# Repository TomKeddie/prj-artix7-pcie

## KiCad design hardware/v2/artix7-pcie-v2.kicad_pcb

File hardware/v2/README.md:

# PCIe artix7

## serdes
- x1 pcie connector (check serdes allocation)
- x1 usb3 connector for expanders and RPi
- x1 on SMA connectors
- x1 in loop?

## Power supply
- reuse supply from netv2

## PMODs
- lots

## CMOD
- maybe

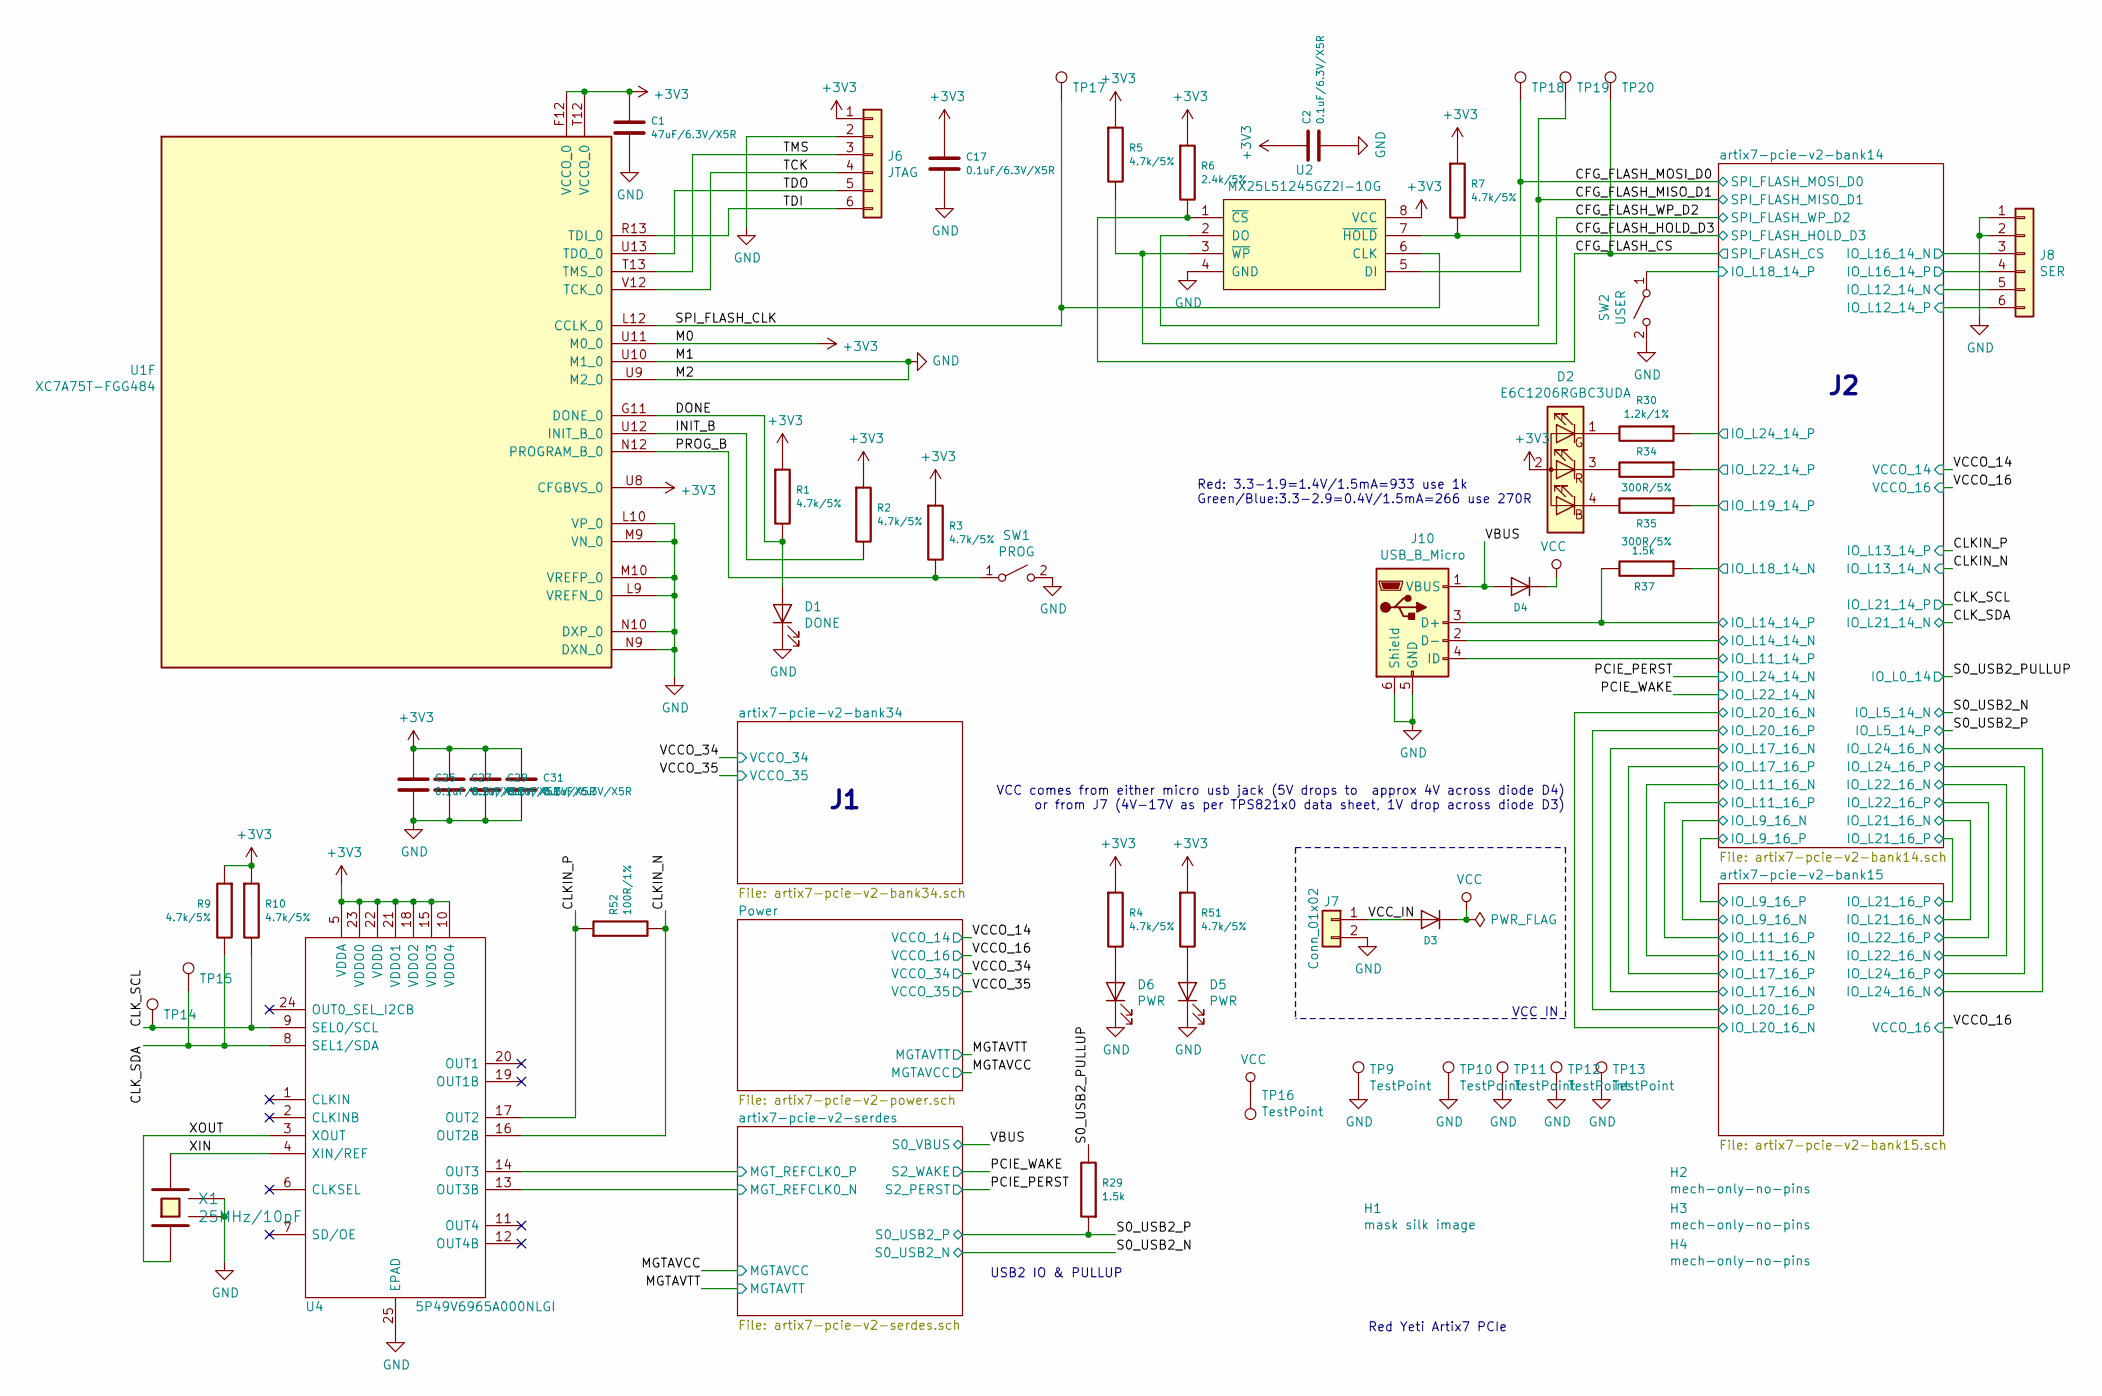
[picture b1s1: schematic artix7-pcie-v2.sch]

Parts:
C1: 47uF/6.3V/X5R; C_1206_3216Metric; LCSC C96123
C2, C17, C25, C27, C29, C31: 0.1uF/6.3V/X5R; C_0402_1005Metric; LCSC C1525
D1: DONE; LED_0402_1005Metric; LCSC C130722
D2: E6C1206RGBC3UDA; LCSC C375571
D3, D4: SBR3U20SA-13; D_SMA; LCSC C146738
D5, D6: PWR; LED_0402_1005Metric; LCSC C130724
H1: mask silk image; mask; LCSC DNP
H2, H3, H4: mech-only-no-pins; JLCPCB_ASSEMBLY_TOOL_HOLE; LCSC DNP
J6: JTAG; PinHeader_2x03_P2.54mm_Vertical; LCSC DNP
J7: Conn_01x02; JST-2-SMD; LCSC DNP
J8: SER; PinHeader_2x03_P2.54mm_Vertical; LCSC DNP
J10: USB_B_Micro; USB_MICRO_TAOBAO_SMD_PTH; LCSC DNP
R1, R2, R3, R4, R5, R7, R9, R10, R51: 4.7k/5%; R_0402_1005Metric; LCSC C25900
R6: 2.4k/5%; R_0402_1005Metric; LCSC C25882
R29, R37: 1.5k; R_0402_1005Metric; LCSC C25867
R30: 1.2k/1%; R_0402_1005Metric; LCSC C25862
R34, R35: 300R/5%; R_0402_1005Metric; LCSC C25102
R52: 100R/1%; R_0402_1005Metric; LCSC C25076
SW1: PROG; SW_Push_1P1T_NO_Vertical_Wuerth_434133025816; LCSC DNP
SW2: USER; SW_Push_1P1T_NO_Vertical_Wuerth_434133025816; LCSC DNP
TP9: TestPoint; TestPoint_Loop_D2.50mm_Drill1.0mm; LCSC DNP
TP10, TP11, TP12, TP13: TestPoint; MountingHole_2.7mm_M2.5_DIN965_Pad; LCSC DNP
TP14: SCL; TestPoint_Pad_D1.5mm; LCSC DNP
TP15: SDA; TestPoint_Pad_D1.5mm; LCSC DNP
TP16, TP17, TP18, TP19, TP20: TestPoint; TestPoint_Pad_D1.5mm; LCSC DNP
U1: XC7A75T-FGG484; Xilinx_FGG484; LCSC DNP
U2: MX25L51245GZ2I-10G; WSON-8-1EP_8x6mm_P1.27mm; LCSC DNP
U4: 5P49V6965A000NLGI; QFN50P400X400X100-25N-D; Mouser Part Number 972-49V6965A000NLGI
X1: 25MHz/10pF; Crystal_SMD_3225-4Pin_3.2x2.5mm; LCSC C9006

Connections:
+3V3: C1.1, C2.1, C17.1, C25.1, C27.1, C29.1, C31.1, D2.2 (A), J6.1, R1.1, R2.1, R3.1, R4.1, R5.1, R6.1, R7.1, R9.1, R10.1, R51.1, U1.F12 (VCCO_0), U1.T12 (VCCO_0), U1.U8 (CFGBVS_0), U1.U11 (M0_0), U2.8 (VCC), U4.5 (VDDA), U4.10 (VDDO4), U4.15 (VDDO3), U4.18 (VDDO2), U4.21 (VDDO1), U4.22 (VDDD), U4.23 (VDDO0); also elsewhere on the board
/CFG_FLASH_CS: R6.2, TP20.1, U2.1 (~CS); also elsewhere on the board
/CFG_FLASH_HOLD_D3: R7.2, U2.7 (~HOLD); also elsewhere on the board
/CFG_FLASH_MISO_D1: TP19.1, U2.2 (DO); also elsewhere on the board
/CFG_FLASH_MOSI_D0: TP18.1, U2.5 (DI); also elsewhere on the board
/CFG_FLASH_WP_D2: R5.2, U2.3 (~WP); also elsewhere on the board
/CLKIN_N: R52.2, U4.16 (OUT2B); also elsewhere on the board
/CLKIN_P: R52.1, U4.17 (OUT2); also elsewhere on the board
/CLK_SCL: R10.2, TP14.1, U4.9 (SEL0/SCL); also elsewhere on the board
/CLK_SDA: R9.2, TP15.1, U4.8 (SEL1/SDA); also elsewhere on the board
/DONE: D1.2 (A), R1.2, U1.G11 (DONE_0)
/INIT_B: R2.2, U1.U12 (INIT_B_0)
/PROG_B: R3.2, SW1.1 (A), U1.N12 (PROGRAM_B_0)
/S0_USB2_P: R29.1; also elsewhere on the board
/S0_USB2_PULLUP: R29.2; also elsewhere on the board
/SPI_FLASH_CLK: TP17.1, U1.L12 (CCLK_0), U2.6 (CLK)
/TCK: J6.4, U1.V12 (TCK_0)
/TDI: J6.6, U1.R13 (TDI_0)
/TDO: J6.5, U1.U13 (TDO_0)
/TMS: J6.3, U1.T13 (TMS_0)
/VBUS: D4.2 (A), J10.1 (VBUS); also elsewhere on the board
/VCC_IN: D3.2 (A), J7.1
/XIN: U4.4 (XIN/REF), X1.3
/XOUT: U4.3 (XOUT), X1.1
/artix7-pcie-v2-bank14/IO_L11_14_P: J10.4 (ID); also elsewhere on the board
/artix7-pcie-v2-bank14/IO_L12_14_N: J8.5; also elsewhere on the board
/artix7-pcie-v2-bank14/IO_L12_14_P: J8.6; also elsewhere on the board
/artix7-pcie-v2-bank14/IO_L14_14_N: J10.2 (D-); also elsewhere on the board
/artix7-pcie-v2-bank14/IO_L14_14_P: J10.3 (D+), R37.2; also elsewhere on the board
/artix7-pcie-v2-bank14/IO_L16_14_N: J8.3; also elsewhere on the board
/artix7-pcie-v2-bank14/IO_L16_14_P: J8.4; also elsewhere on the board
/artix7-pcie-v2-bank14/IO_L18_14_N: R37.1; also elsewhere on the board
/artix7-pcie-v2-bank14/IO_L18_14_P: SW2.1 (A); also elsewhere on the board
/artix7-pcie-v2-bank14/IO_L19_14_P: R35.1; also elsewhere on the board
/artix7-pcie-v2-bank14/IO_L22_14_P: R34.1; also elsewhere on the board
/artix7-pcie-v2-bank14/IO_L24_14_P: R30.1; also elsewhere on the board
/artix7-pcie-v2-serdes/MGT_REFCLK0_N: U4.13 (OUT3B); also elsewhere on the board
/artix7-pcie-v2-serdes/MGT_REFCLK0_P: U4.14 (OUT3); also elsewhere on the board
GND: C1.2, C2.2, C17.2, C25.2, C27.2, C29.2, C31.2, D1.1 (K), D5.1 (K), D6.1 (K), J6.2, J7.2, J8.1, J8.2, J10.5 (GND), J10.6 (Shield), SW1.2 (B), SW2.2 (B), TP9.1, TP10.1, TP11.1, TP12.1, TP13.1, U1.L9 (VREFN_0), U1.L10 (VP_0), U1.M9 (VN_0), U1.M10 (VREFP_0), U1.N9 (DXN_0), U1.N10 (DXP_0), U1.U9 (M2_0), U1.U10 (M1_0), U2.4 (GND), U4.25 (EPAD), X1.2 (GND), X1.4 (GND); also elsewhere on the board
unnamed: D2.1 (G), R30.2
unnamed: D2.3 (R), R34.2
unnamed: D2.4 (B), R35.2
unnamed: D5.2 (A), R51.2
unnamed: D6.2 (A), R4.2
VCC: D3.1 (K), D4.1 (K), TP16.1; also elsewhere on the board

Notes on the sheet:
USB2 IO & PULLUP
VCC IN
Red: 3.3-1.9=1.4V/1.5mA=933 use 1k Green/Blue:3.3-2.9=0.4V/1.5mA=266 use 270R
VCC comes from either micro usb jack (5V drops to approx 4V across diode D4) or from J7 (4V-17V as per TPS821x0 data sheet, 1V drop across diode D3)
Red Yeti Artix7 PCIe

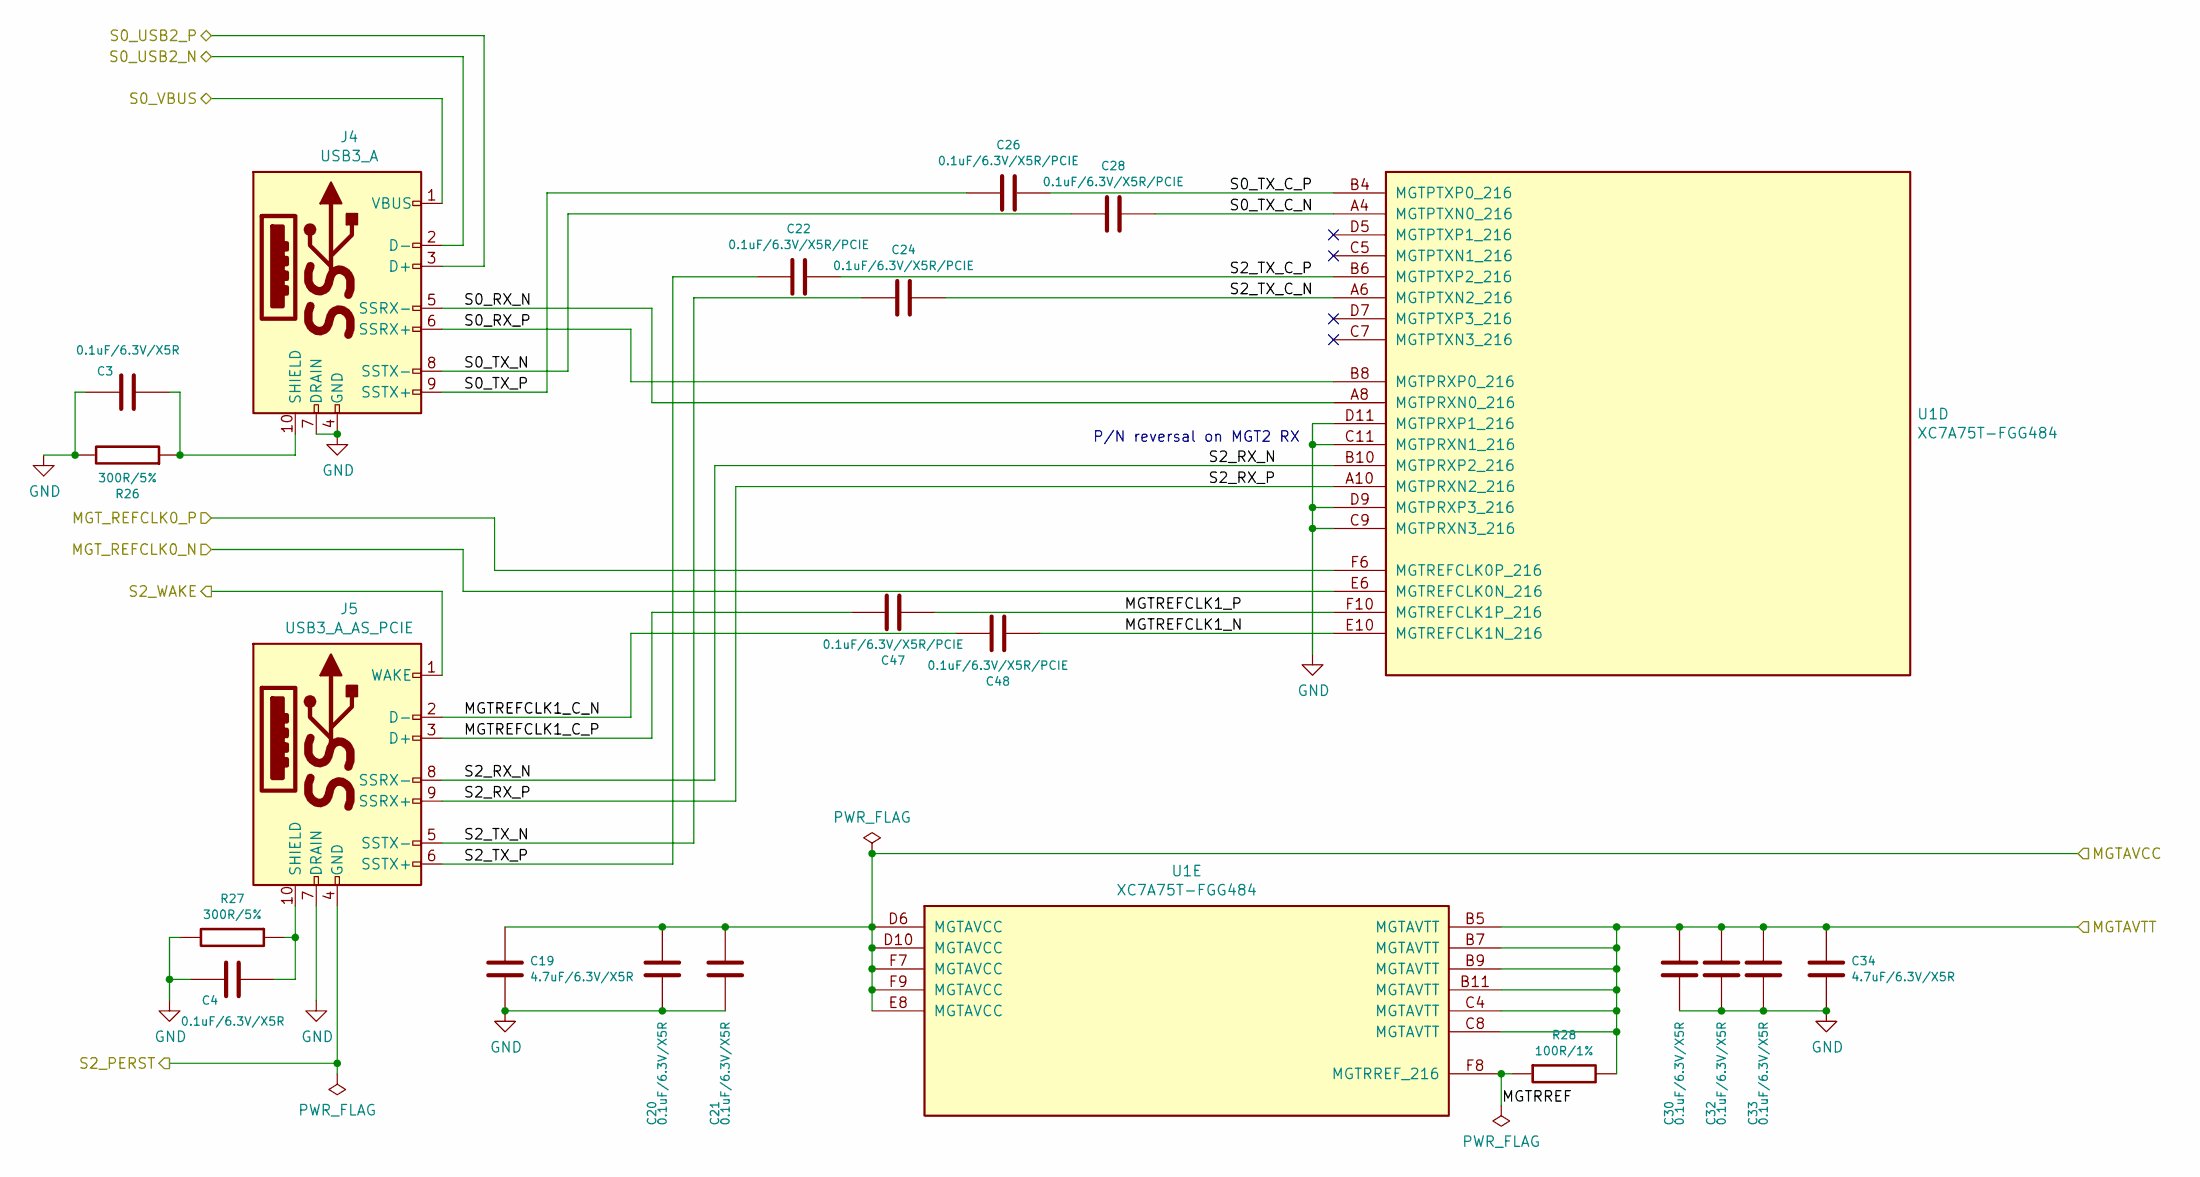
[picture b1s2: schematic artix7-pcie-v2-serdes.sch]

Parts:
C3, C4, C20, C21, C30, C32, C33: 0.1uF/6.3V/X5R; C_0402_1005Metric; LCSC C1525
C19, C34: 4.7uF/6.3V/X5R; C_0402_1005Metric; LCSC C23733
C22, C24, C26, C28, C47, C48: 0.1uF/6.3V/X5R/PCIE; C_0402_1005Metric; LCSC C1525
J4: USB3_A; USB3_A_Aliexpress; Digikey 2057-USB-A3-S-RA-ND
J5: USB3_A_AS_PCIE; USB3_A_Aliexpress; Digikey 2057-USB-A3-S-RA-ND
R26, R27: 300R/5%; R_0402_1005Metric; LCSC C25102
R28: 100R/1%; R_0402_1005Metric; LCSC C25076
U1: XC7A75T-FGG484; Xilinx_FGG484; LCSC DNP

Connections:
+1V0: C19.1, C20.1, C21.1, U1.D6 (MGTAVCC), U1.D10 (MGTAVCC), U1.E8 (MGTAVCC), U1.F7 (MGTAVCC), U1.F9 (MGTAVCC); also elsewhere on the board
/MGTAVTT: C30.1, C32.1, C33.1, C34.1, R28.2, U1.B5 (MGTAVTT), U1.B7 (MGTAVTT), U1.B9 (MGTAVTT), U1.B11 (MGTAVTT), U1.C4 (MGTAVTT), U1.C8 (MGTAVTT); also elsewhere on the board
/PCIE_PERST: J5.4 (GND); also elsewhere on the board
/PCIE_WAKE: J5.1 (WAKE); also elsewhere on the board
/S0_USB2_N: J4.2 (D-); also elsewhere on the board
/S0_USB2_P: J4.3 (D+); also elsewhere on the board
/VBUS: J4.1 (VBUS); also elsewhere on the board
/artix7-pcie-v2-serdes/MGTREFCLK1_C_N: C48.2, J5.2 (D-)
/artix7-pcie-v2-serdes/MGTREFCLK1_C_P: C47.2, J5.3 (D+)
/artix7-pcie-v2-serdes/MGTREFCLK1_N: C48.1, U1.E10 (MGTREFCLK1N_216)
/artix7-pcie-v2-serdes/MGTREFCLK1_P: C47.1, U1.F10 (MGTREFCLK1P_216)
/artix7-pcie-v2-serdes/MGTRREF: R28.1, U1.F8 (MGTRREF_216)
/artix7-pcie-v2-serdes/MGT_REFCLK0_N: U1.E6 (MGTREFCLK0N_216); also elsewhere on the board
/artix7-pcie-v2-serdes/MGT_REFCLK0_P: U1.F6 (MGTREFCLK0P_216); also elsewhere on the board
/artix7-pcie-v2-serdes/S0_RX_N: J4.5 (SSRX-), U1.A8 (MGTPRXN0_216)
/artix7-pcie-v2-serdes/S0_RX_P: J4.6 (SSRX+), U1.B8 (MGTPRXP0_216)
/artix7-pcie-v2-serdes/S0_TX_C_N: C28.1, U1.A4 (MGTPTXN0_216)
/artix7-pcie-v2-serdes/S0_TX_C_P: C26.1, U1.B4 (MGTPTXP0_216)
/artix7-pcie-v2-serdes/S0_TX_N: C28.2, J4.8 (SSTX-)
/artix7-pcie-v2-serdes/S0_TX_P: C26.2, J4.9 (SSTX+)
/artix7-pcie-v2-serdes/S2_RX_N: J5.8 (SSRX-), U1.B10 (MGTPRXP2_216)
/artix7-pcie-v2-serdes/S2_RX_P: J5.9 (SSRX+), U1.A10 (MGTPRXN2_216)
/artix7-pcie-v2-serdes/S2_TX_C_N: C24.1, U1.A6 (MGTPTXN2_216)
/artix7-pcie-v2-serdes/S2_TX_C_P: C22.1, U1.B6 (MGTPTXP2_216)
/artix7-pcie-v2-serdes/S2_TX_N: C24.2, J5.5 (SSTX-)
/artix7-pcie-v2-serdes/S2_TX_P: C22.2, J5.6 (SSTX+)
GND: C3.2, C4.2, C19.2, C20.2, C21.2, C30.2, C32.2, C33.2, C34.2, J4.4 (GND), J4.7 (DRAIN), J5.7 (DRAIN), R26.2, R27.2, U1.C9 (MGTPRXN3_216), U1.C11 (MGTPRXN1_216), U1.D9 (MGTPRXP3_216), U1.D11 (MGTPRXP1_216); also elsewhere on the board
unnamed: C3.1, J4.10 (SHIELD), R26.1
unnamed: C4.1, J5.10 (SHIELD), R27.1

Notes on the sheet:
P/N reversal on MGT2 RX

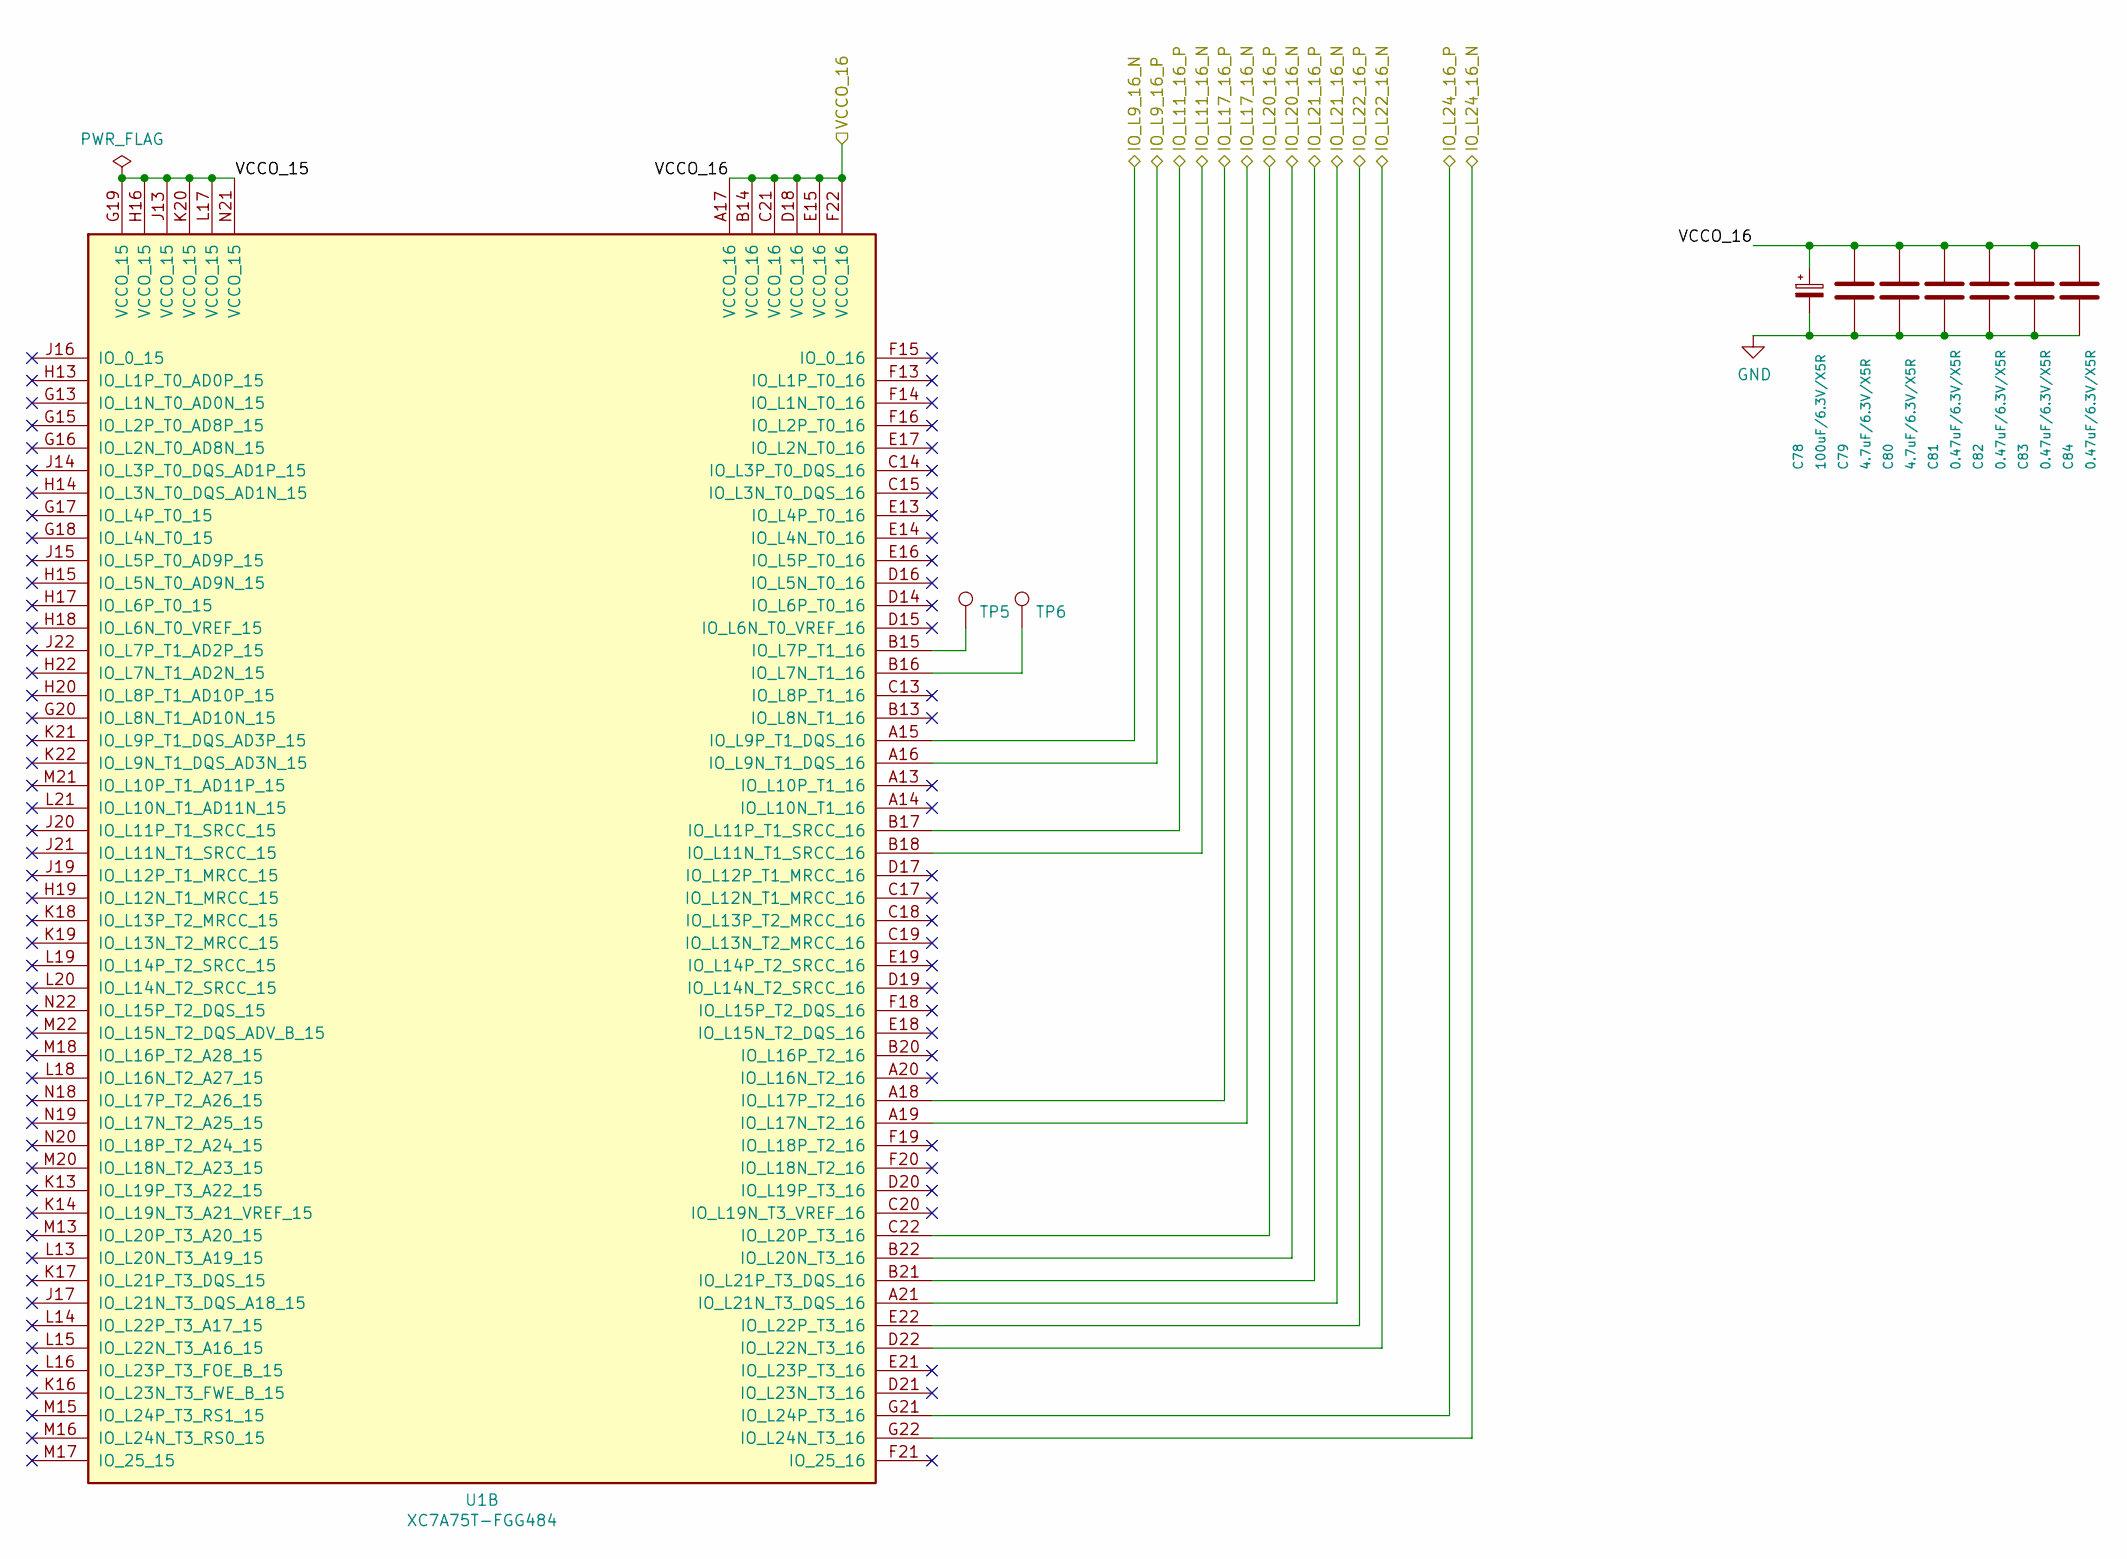
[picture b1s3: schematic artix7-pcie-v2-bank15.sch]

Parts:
C78: 100uF/6.3V/X5R; CP_EIA-3528-15_AVX-H; LCSC C16133
C79, C80: 4.7uF/6.3V/X5R; C_0402_1005Metric; LCSC C23733
C81, C82, C83, C84: 0.47uF/6.3V/X5R; C_0402_1005Metric; LCSC C47339
TP5, TP6: TestPoint; TestPoint_Pad_D1.5mm; LCSC DNP
U1: XC7A75T-FGG484; Xilinx_FGG484; LCSC DNP

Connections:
/VCCO_16: C78.1, C79.1, C80.1, C81.1, C82.1, C83.1, C84.1, U1.A17 (VCCO_16), U1.B14 (VCCO_16), U1.C21 (VCCO_16), U1.D18 (VCCO_16), U1.E15 (VCCO_16), U1.F22 (VCCO_16); also elsewhere on the board
/artix7-pcie-v2-bank14/IO_L9_16_N: U1.A15 (IO_L9P_T1_DQS_16); also elsewhere on the board
/artix7-pcie-v2-bank14/IO_L9_16_P: U1.A16 (IO_L9N_T1_DQS_16); also elsewhere on the board
/artix7-pcie-v2-bank14/IO_L11_16_N: U1.B18 (IO_L11N_T1_SRCC_16); also elsewhere on the board
/artix7-pcie-v2-bank14/IO_L11_16_P: U1.B17 (IO_L11P_T1_SRCC_16); also elsewhere on the board
/artix7-pcie-v2-bank14/IO_L17_16_N: U1.A19 (IO_L17N_T2_16); also elsewhere on the board
/artix7-pcie-v2-bank14/IO_L17_16_P: U1.A18 (IO_L17P_T2_16); also elsewhere on the board
/artix7-pcie-v2-bank14/IO_L20_16_N: U1.B22 (IO_L20N_T3_16); also elsewhere on the board
/artix7-pcie-v2-bank14/IO_L20_16_P: U1.C22 (IO_L20P_T3_16); also elsewhere on the board
/artix7-pcie-v2-bank14/IO_L21_16_N: U1.A21 (IO_L21N_T3_DQS_16); also elsewhere on the board
/artix7-pcie-v2-bank14/IO_L21_16_P: U1.B21 (IO_L21P_T3_DQS_16); also elsewhere on the board
/artix7-pcie-v2-bank14/IO_L22_16_N: U1.D22 (IO_L22N_T3_16); also elsewhere on the board
/artix7-pcie-v2-bank14/IO_L22_16_P: U1.E22 (IO_L22P_T3_16); also elsewhere on the board
/artix7-pcie-v2-bank14/IO_L24_16_N: U1.G22 (IO_L24N_T3_16); also elsewhere on the board
/artix7-pcie-v2-bank14/IO_L24_16_P: U1.G21 (IO_L24P_T3_16); also elsewhere on the board
/artix7-pcie-v2-bank15/VCCO_15: U1.G19 (VCCO_15), U1.H16 (VCCO_15), U1.J13 (VCCO_15), U1.K20 (VCCO_15), U1.L17 (VCCO_15), U1.N21 (VCCO_15)
GND: C78.2, C79.2, C80.2, C81.2, C82.2, C83.2, C84.2; also elsewhere on the board
unnamed: TP5.1, U1.B15 (IO_L7P_T1_16)
unnamed: TP6.1, U1.B16 (IO_L7N_T1_16)

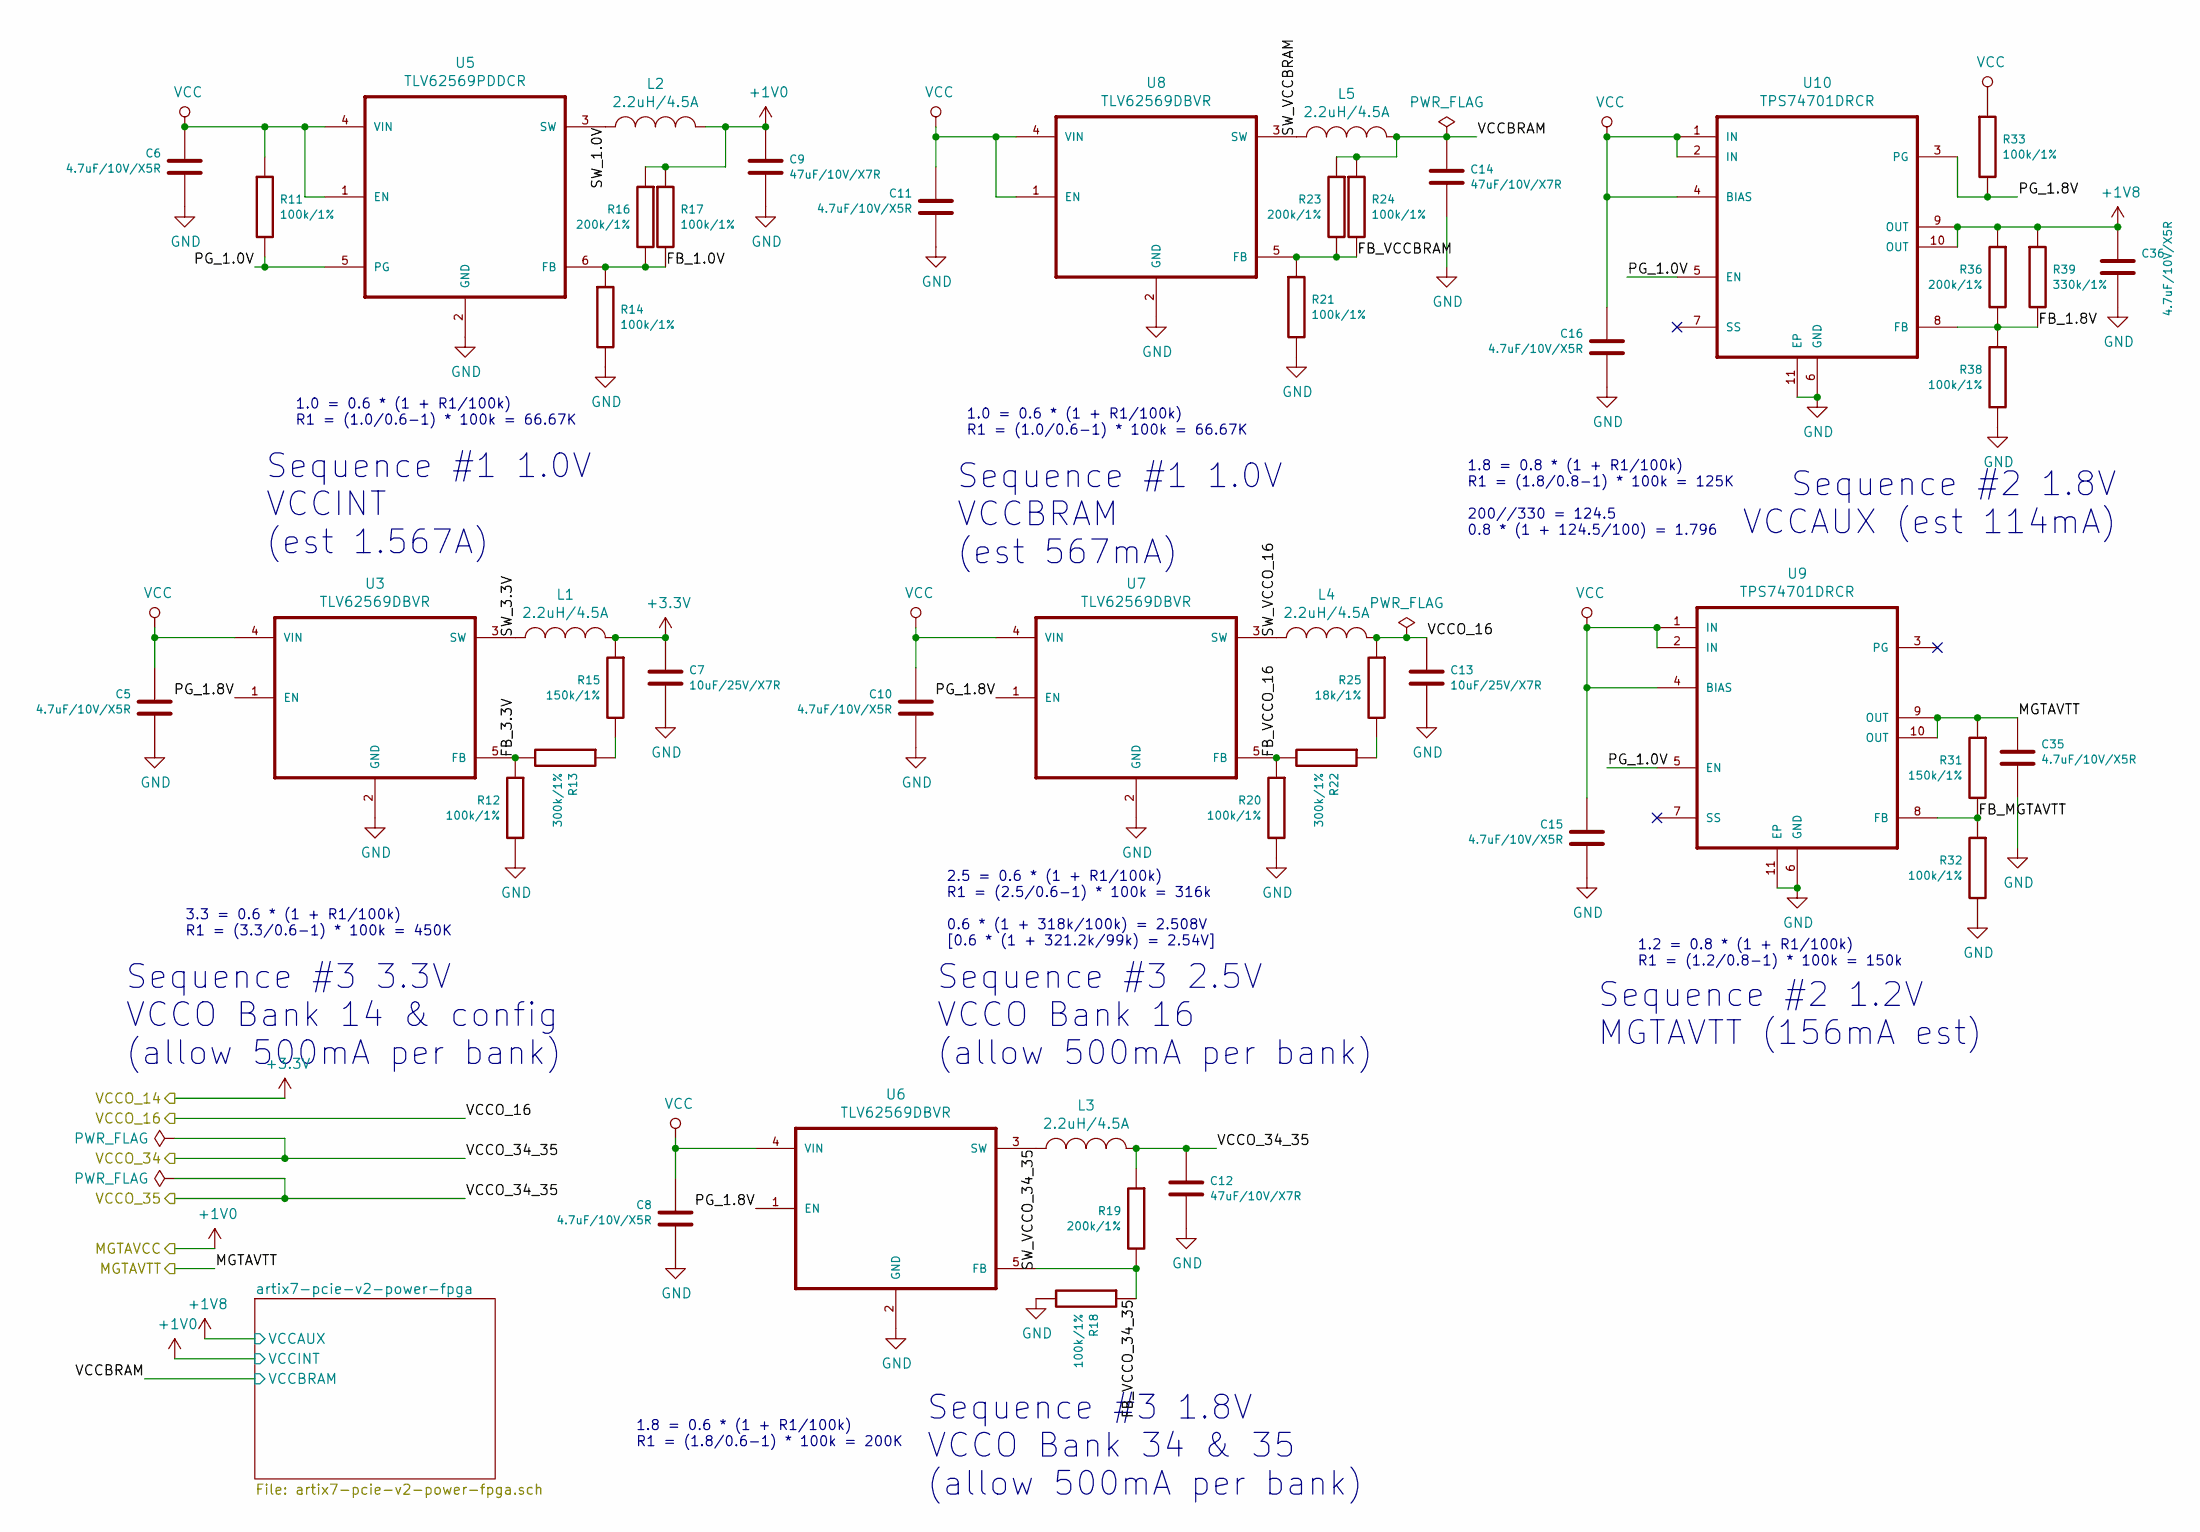
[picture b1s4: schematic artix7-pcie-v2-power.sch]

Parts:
C5, C6, C8, C10, C11, C15, C16, C35, C36: 4.7uF/10V/X5R; C_0402_1005Metric; LCSC C23733
C7, C13: 10uF/25V/X7R; C_1206_3216Metric; MFGPN C3216X7R1E106M160AE; LCSC C13585
C9, C12, C14: 47uF/10V/X7R; C_1206_3216Metric; LCSC C96123
L1, L2, L3, L4, L5: 2.2uH/4.5A; L_MWSA0518S; MPN MWSA0518S-2R2MT; LCSC C408345
R11, R12, R14, R17, R18, R20, R21, R24, R32, R33, R38: 100k/1%; R_0402_1005Metric; LCSC C25741
R13, R22: 300k/1%; R_0402_1005Metric; LCSC C25774
R15, R31: 150k/1%; R_0402_1005Metric; LCSC C25755
R16, R19, R23, R36: 200k/1%; R_0402_1005Metric; LCSC C25764
R25: 18k/1%; R_0402_1005Metric; LCSC C25762
R39: 330k/1%; R_0402_1005Metric; LCSC C25778
U3, U6, U7, U8: TLV62569DBVR; SOT95P280X145-5N; LCSC C141836
U5: TLV62569PDDCR; SOT95P280X110-6N; LCSC DNP
U9, U10: TPS74701DRCR; 16624-01YE; LCSC C105262

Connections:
+1V0: C9.2, L2.2, R16.1, R17.1; also elsewhere on the board
+1V8: C36.2, R36.1, R39.1, U10.9 (OUT), U10.10 (OUT); also elsewhere on the board
+3V3: C7.2, L1.2, R15.1; also elsewhere on the board
/MGTAVTT: C35.2, R31.1, U9.9 (OUT), U9.10 (OUT); also elsewhere on the board
/Power/FB_1.0V: R14.1, R16.2, R17.2, U5.6 (FB)
/Power/FB_1.8V: R36.2, R38.1, R39.2, U10.8 (FB)
/Power/FB_3.3V: R12.1, R13.2, U3.5 (FB)
/Power/FB_MGTAVTT: R31.2, R32.1, U9.8 (FB)
/Power/FB_VCCBRAM: R21.1, R23.2, R24.2, U8.5 (FB)
/Power/FB_VCCO_16: R20.1, R22.2, U7.5 (FB)
/Power/FB_VCCO_34_35: R18.1, R19.2, U6.5 (FB)
/Power/PG_1.0V: R11.2, U5.5 (PG), U9.5 (EN), U10.5 (EN)
/Power/PG_1.8V: R33.2, U3.1 (EN), U6.1 (EN), U7.1 (EN), U10.3 (PG)
/Power/SW_1.0V: L2.1, U5.3 (SW)
/Power/SW_3.3V: L1.1, U3.3 (SW)
/Power/SW_VCCBRAM: L5.1, U8.3 (SW)
/Power/SW_VCCO_16: L4.1, U7.3 (SW)
/Power/SW_VCCO_34_35: L3.1, U6.3 (SW)
/Power/VCCBRAM: C14.2, L5.2, R23.1, R24.1; also elsewhere on the board
/VCCO_16: C13.2, L4.2, R25.1; also elsewhere on the board
/VCCO_34: C12.2, L3.2, R19.1; also elsewhere on the board
GND: C5.1, C6.1, C7.1, C8.1, C9.1, C10.1, C11.1, C12.1, C13.1, C14.1, C15.1, C16.1, C35.1, C36.1, R12.2, R14.2, R18.2, R20.2, R21.2, R32.2, R38.2, U3.2 (GND), U5.2 (GND), U6.2 (GND), U7.2 (GND), U8.2 (GND), U9.6 (GND), U9.11 (EP), U10.6 (GND), U10.11 (EP); also elsewhere on the board
unnamed: R13.1, R15.2
unnamed: R22.1, R25.2
VCC: C5.2, C6.2, C8.2, C10.2, C11.2, C15.2, C16.2, R11.1, R33.1, U3.4 (VIN), U5.1 (EN), U5.4 (VIN), U6.4 (VIN), U7.4 (VIN), U8.1 (EN), U8.4 (VIN), U9.1 (IN), U9.2 (IN), U9.4 (BIAS), U10.1 (IN), U10.2 (IN), U10.4 (BIAS); also elsewhere on the board

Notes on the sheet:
1.0 = 0.6 * (1 + R1/100k) R1 = (1.0/0.6-1) * 100k = 66.67K
Sequence #1 1.0V VCCINT (est 1.567A)
Sequence #1 1.0V VCCBRAM (est 567mA)
Sequence #2 1.8V VCCAUX (est 114mA)
1.8 = 0.8 * (1 + R1/100k) R1 = (1.8/0.8-1) * 100k = 125K 200//330 = 124.5 0.8 * (1 + 124.5/100) = 1.796
1.2 = 0.8 * (1 + R1/100k) R1 = (1.2/0.8-1) * 100k = 150k
Sequence #2 1.2V MGTAVTT (156mA est)
Sequence #3 3.3V VCCO Bank 14 & config (allow 500mA per bank)
3.3 = 0.6 * (1 + R1/100k) R1 = (3.3/0.6-1) * 100k = 450K
2.5 = 0.6 * (1 + R1/100k) R1 = (2.5/0.6-1) * 100k = 316k 0.6 * (1 + 318k/100k) = 2.508V [0.6 * (1 + 321.2k/99k) = 2.54V]
Sequence #3 2.5V VCCO Bank 16 (allow 500mA per bank)
Sequence #3 1.8V VCCO Bank 34 & 35 (allow 500mA per bank)
1.8 = 0.6 * (1 + R1/100k) R1 = (1.8/0.6-1) * 100k = 200K
